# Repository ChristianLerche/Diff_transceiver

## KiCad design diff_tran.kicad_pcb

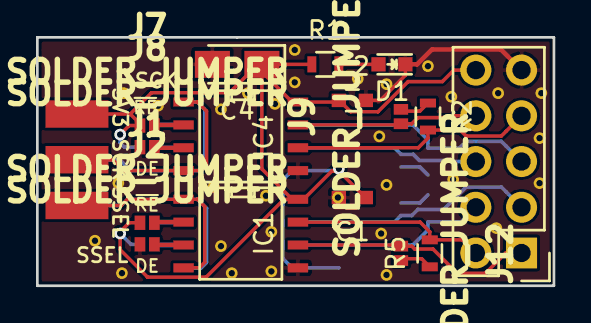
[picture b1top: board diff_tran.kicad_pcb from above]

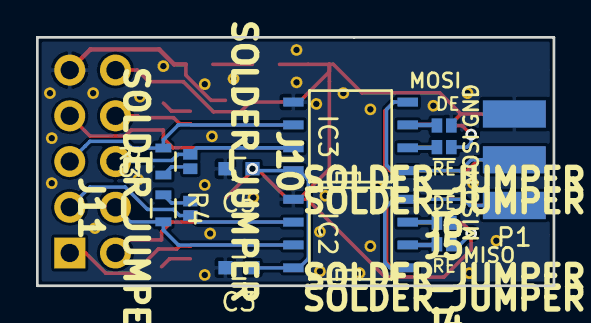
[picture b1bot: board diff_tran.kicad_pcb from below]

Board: 2 copper layers, 28.7 x 13.8 mm, 29 parts (13 on the bottom side), 27 nets.

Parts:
C1, C2, C3, C5: 100nF; C_0603
C4: 10uF; Tantalum_Case-A_EIA-3216-18_Reflow
D1: RED_LED; LED_0603
IC1, IC2, IC3, IC4: SN65LVDM176; SOIC-8-N
J1, J2, J3, J4, J5, J6, J7, J8, J9, J10, J11, J12: SOLDER_JUMPER; Lerche_2PsolderJumper
P1: CONN_02X03; Lerche_2x3p_2.54mm_PCBedge
P2: CONN_02X05; Pin_Header_Straight_2x05
R1: 330; R_0603
R2, R3, R4, R5: 100; R_0603

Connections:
+3V3: C1.1, C2.1, C3.1, C4.1, C5.1, IC1.8, IC2.8, IC3.8, IC4.8, J1.1, J3.1, J5.1, J7.1, P1.6, P2.10, R1.1
GND: C1.2, C2.2, C3.2, C4.2, C5.2, D1.1, IC1.5, IC2.5, IC3.5, IC4.5, J2.1, J4.1, J6.1, J8.1, P1.5, P2.9
MISO: IC2.1, IC2.4, P1.1
MOSI: IC3.1, IC3.4, P1.3
unnamed: D1.2, R1.2
unnamed: IC1.2, J1.2
unnamed: IC1.3, J2.2
unnamed: IC1.6, J12.1, P2.1
unnamed: IC1.7, P2.2, R5.2
unnamed: IC2.2, J3.2
unnamed: IC2.3, J4.2
unnamed: IC2.6, J11.1, P2.3
unnamed: IC2.7, P2.4, R4.2
unnamed: IC3.2, J5.2
unnamed: IC3.3, J6.2
unnamed: IC3.6, P2.5, R3.2
unnamed: IC3.7, J10.1, P2.6
unnamed: IC4.2, J7.2
unnamed: IC4.3, J8.2
unnamed: IC4.6, P2.7, R2.2
unnamed: IC4.7, J9.1, P2.8
unnamed: J9.2, R2.1
unnamed: J10.2, R3.1
unnamed: J11.2, R4.1
unnamed: J12.2, R5.1
SCK: IC4.1, IC4.4, P1.4
SSEL: IC1.1, IC1.4, P1.2

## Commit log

2016-12-02 :boom::camel: Added .gitattributes & .gitignore files
2016-12-02 Start of git
    Start of git
2016-12-02 Ongoing project
    Ongoing project
2017-01-27 Tracks
2017-03-16 Added some text, almost finished
    Added some text, almost finished
